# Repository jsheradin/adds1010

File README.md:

# adds1010
Modernization of an ADDS 1010 terminal keyboard

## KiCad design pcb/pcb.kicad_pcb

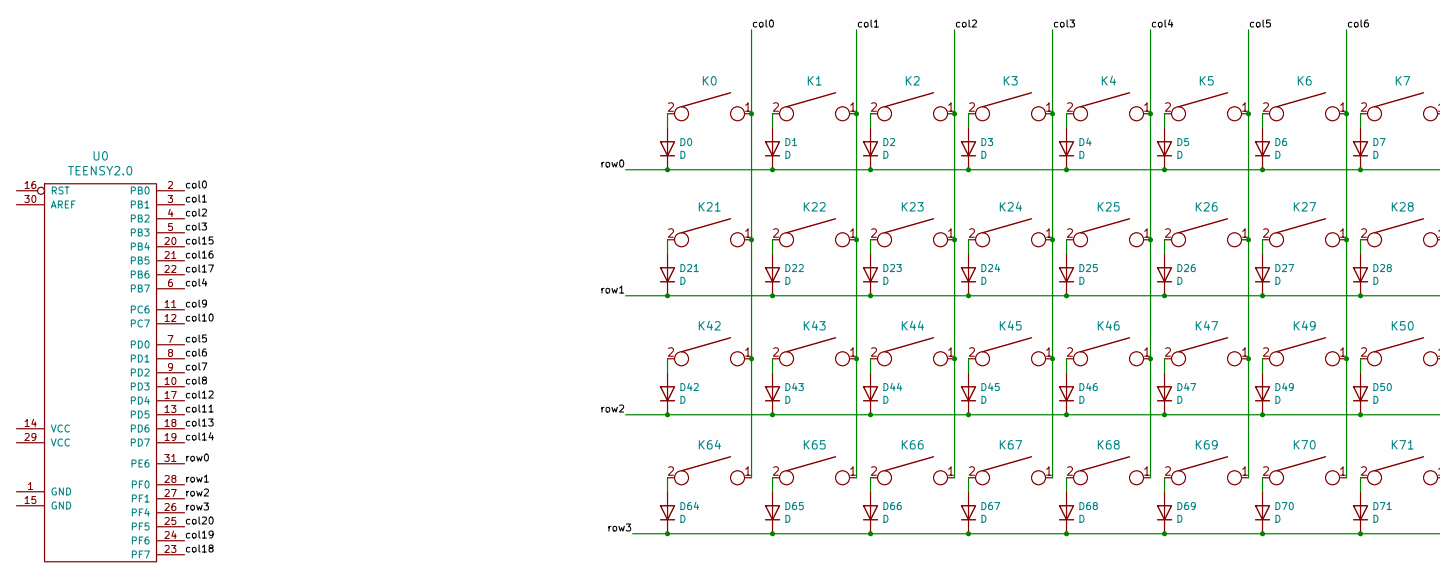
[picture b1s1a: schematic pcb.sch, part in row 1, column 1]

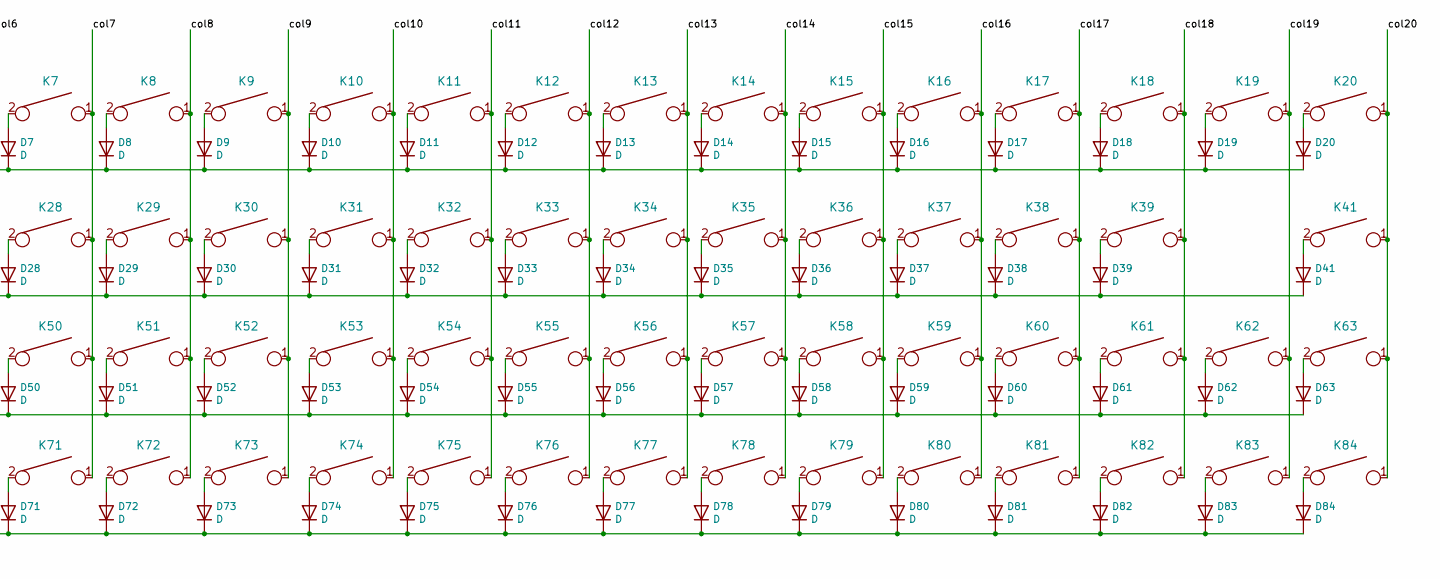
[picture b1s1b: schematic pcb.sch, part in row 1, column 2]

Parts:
D0, D1, D2, D3, D4, D5, D6, D7, D8, D9, D10, D11, D12, D13, D14, D15, D16, D17, D18, D19, D20, D21, D22, D23, D24, D25, D26, D27, D28, D29, D30, D31, D32, D33, D34, D35, D36, D37, D38, D39, D41, D42, D43, D44, D45, D46, D47, D49, D50, D51, D52, D53, D54, D55, D56, D57, D58, D59, D60, D61, D62, D63, D64, D65, D66, D67, D68, D69, D70, D71, D72, D73, D74, D75, D76, D77, D78, D79, D80, D81, D82, D83, D84: D; D_SOD123_axial
K0, K1, K2, K3, K4, K5, K6, K7, K8, K9, K10, K11, K12, K13, K14, K15, K16, K17, K18, K19, K20, K21, K22, K23, K24, K25, K26, K27, K28, K29, K30, K31, K32, K33, K34, K35, K36, K37, K38, K39, K41, K42, K43, K44, K45, K46, K47, K49, K50, K51, K52, K53, K54, K55, K56, K57, K58, K59, K60, K61, K62, K63, K64, K65, K66, K67, K68, K69, K70, K71, K72, K73, K74, K75, K76, K77, K78, K79, K80, K81, K82, K83, K84: KEYSW; Space_Invaders
U0: TEENSY2.0; Teensy2.0

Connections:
/col0: K0.1, K21.1, K42.1, K64.1, U0.2 (PB0)
/col1: K1.1, K22.1, K43.1, K65.1, U0.3 (PB1)
/col2: K2.1, K23.1, K44.1, K66.1, U0.4 (PB2)
/col3: K3.1, K24.1, K45.1, K67.1, U0.5 (PB3)
/col4: K4.1, K25.1, K46.1, K68.1, U0.6 (PB7)
/col5: K5.1, K26.1, K47.1, K69.1, U0.7 (PD0)
/col6: K6.1, K27.1, K49.1, K70.1, U0.8 (PD1)
/col7: K7.1, K28.1, K50.1, K71.1, U0.9 (PD2)
/col8: K8.1, K29.1, K51.1, K72.1, U0.10 (PD3)
/col9: K9.1, K30.1, K52.1, K73.1, U0.11 (PC6)
/col10: K10.1, K31.1, K53.1, K74.1, U0.12 (PC7)
/col11: K11.1, K32.1, K54.1, K75.1, U0.13 (PD5)
/col12: K12.1, K33.1, K55.1, K76.1, U0.17 (PD4)
/col13: K13.1, K34.1, K56.1, K77.1, U0.18 (PD6)
/col14: K14.1, K35.1, K57.1, K78.1, U0.19 (PD7)
/col15: K15.1, K36.1, K58.1, K79.1, U0.20 (PB4)
/col16: K16.1, K37.1, K59.1, K80.1, U0.21 (PB5)
/col17: K17.1, K38.1, K60.1, K81.1, U0.22 (PB6)
/col18: K18.1, K39.1, K61.1, K82.1, U0.23 (PF7)
/col19: K19.1, K62.1, K83.1, U0.24 (PF6)
/col20: K20.1, K41.1, K63.1, K84.1, U0.25 (PF5)
/row0: D0.1 (K), D1.1 (K), D2.1 (K), D3.1 (K), D4.1 (K), D5.1 (K), D6.1 (K), D7.1 (K), D8.1 (K), D9.1 (K), D10.1 (K), D11.1 (K), D12.1 (K), D13.1 (K), D14.1 (K), D15.1 (K), D16.1 (K), D17.1 (K), D18.1 (K), D19.1 (K), D20.1 (K), U0.31 (PE6)
/row1: D21.1 (K), D22.1 (K), D23.1 (K), D24.1 (K), D25.1 (K), D26.1 (K), D27.1 (K), D28.1 (K), D29.1 (K), D30.1 (K), D31.1 (K), D32.1 (K), D33.1 (K), D34.1 (K), D35.1 (K), D36.1 (K), D37.1 (K), D38.1 (K), D39.1 (K), D41.1 (K), U0.28 (PF0)
/row2: D42.1 (K), D43.1 (K), D44.1 (K), D45.1 (K), D46.1 (K), D47.1 (K), D49.1 (K), D50.1 (K), D51.1 (K), D52.1 (K), D53.1 (K), D54.1 (K), D55.1 (K), D56.1 (K), D57.1 (K), D58.1 (K), D59.1 (K), D60.1 (K), D61.1 (K), D62.1 (K), D63.1 (K), U0.27 (PF1)
/row3: D64.1 (K), D65.1 (K), D66.1 (K), D67.1 (K), D68.1 (K), D69.1 (K), D70.1 (K), D71.1 (K), D72.1 (K), D73.1 (K), D74.1 (K), D75.1 (K), D76.1 (K), D77.1 (K), D78.1 (K), D79.1 (K), D80.1 (K), D81.1 (K), D82.1 (K), D83.1 (K), D84.1 (K), U0.26 (PF4)
unnamed: D0.2 (A), K0.2
unnamed: D1.2 (A), K1.2
unnamed: D2.2 (A), K2.2
unnamed: D3.2 (A), K3.2
unnamed: D4.2 (A), K4.2
unnamed: D5.2 (A), K5.2
unnamed: D6.2 (A), K6.2
unnamed: D7.2 (A), K7.2
unnamed: D8.2 (A), K8.2
unnamed: D9.2 (A), K9.2
unnamed: D10.2 (A), K10.2
unnamed: D11.2 (A), K11.2
unnamed: D12.2 (A), K12.2
unnamed: D13.2 (A), K13.2
unnamed: D14.2 (A), K14.2
unnamed: D15.2 (A), K15.2
unnamed: D16.2 (A), K16.2
unnamed: D17.2 (A), K17.2
unnamed: D18.2 (A), K18.2
unnamed: D19.2 (A), K19.2
unnamed: D20.2 (A), K20.2
unnamed: D21.2 (A), K21.2
unnamed: D22.2 (A), K22.2
unnamed: D23.2 (A), K23.2
unnamed: D24.2 (A), K24.2
unnamed: D25.2 (A), K25.2
unnamed: D26.2 (A), K26.2
unnamed: D27.2 (A), K27.2
unnamed: D28.2 (A), K28.2
unnamed: D29.2 (A), K29.2
unnamed: D30.2 (A), K30.2
unnamed: D31.2 (A), K31.2
unnamed: D32.2 (A), K32.2
unnamed: D33.2 (A), K33.2
unnamed: D34.2 (A), K34.2
unnamed: D35.2 (A), K35.2
unnamed: D36.2 (A), K36.2
unnamed: D37.2 (A), K37.2
unnamed: D38.2 (A), K38.2
unnamed: D39.2 (A), K39.2
unnamed: D41.2 (A), K41.2
unnamed: D42.2 (A), K42.2
unnamed: D43.2 (A), K43.2
unnamed: D44.2 (A), K44.2
unnamed: D45.2 (A), K45.2
unnamed: D46.2 (A), K46.2
unnamed: D47.2 (A), K47.2
unnamed: D49.2 (A), K49.2
unnamed: D50.2 (A), K50.2
unnamed: D51.2 (A), K51.2
unnamed: D52.2 (A), K52.2
unnamed: D53.2 (A), K53.2
unnamed: D54.2 (A), K54.2
unnamed: D55.2 (A), K55.2
unnamed: D56.2 (A), K56.2
unnamed: D57.2 (A), K57.2
unnamed: D58.2 (A), K58.2
unnamed: D59.2 (A), K59.2
unnamed: D60.2 (A), K60.2
unnamed: D61.2 (A), K61.2
unnamed: D62.2 (A), K62.2
unnamed: D63.2 (A), K63.2
unnamed: D64.2 (A), K64.2
unnamed: D65.2 (A), K65.2
unnamed: D66.2 (A), K66.2
unnamed: D67.2 (A), K67.2
unnamed: D68.2 (A), K68.2
unnamed: D69.2 (A), K69.2
unnamed: D70.2 (A), K70.2
unnamed: D71.2 (A), K71.2
unnamed: D72.2 (A), K72.2
unnamed: D73.2 (A), K73.2
unnamed: D74.2 (A), K74.2
unnamed: D75.2 (A), K75.2
unnamed: D76.2 (A), K76.2
unnamed: D77.2 (A), K77.2
unnamed: D78.2 (A), K78.2
unnamed: D79.2 (A), K79.2
unnamed: D80.2 (A), K80.2
unnamed: D81.2 (A), K81.2
unnamed: D82.2 (A), K82.2
unnamed: D83.2 (A), K83.2
unnamed: D84.2 (A), K84.2

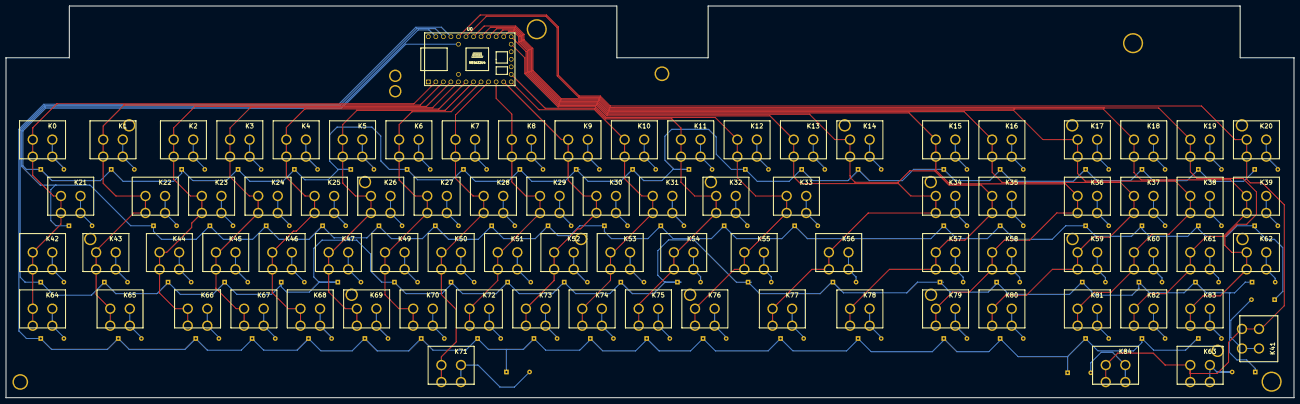
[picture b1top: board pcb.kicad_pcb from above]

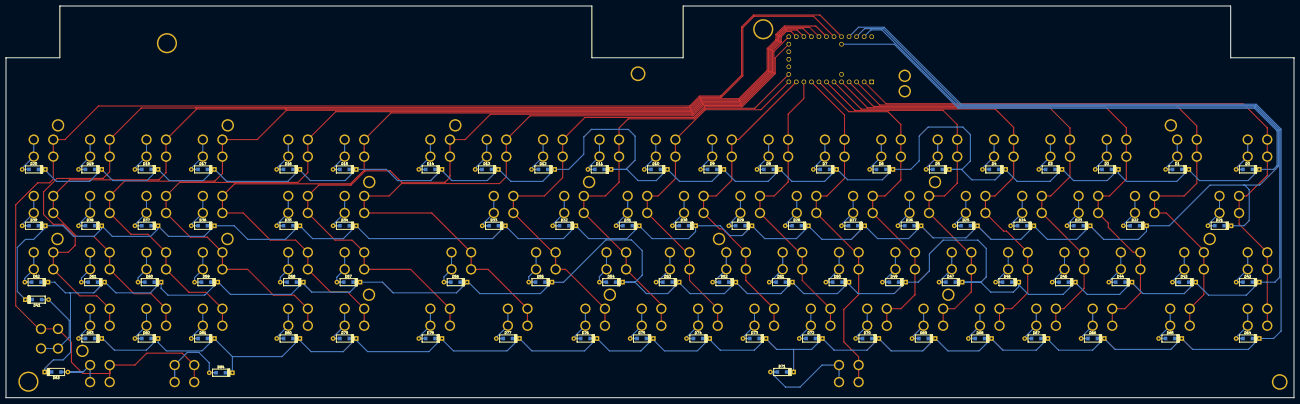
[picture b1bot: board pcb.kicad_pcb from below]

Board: 2 copper layers, 434.2 x 132.0 mm, 189 parts (83 on the bottom side), 108 nets.

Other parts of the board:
3.0mm, 3.0mm#2, 3.0mm#3, 3.0mm#4, 3.0mm#5, 3.0mm#6, 3.0mm#7, 3.0mm#8, 3.0mm#9, 3.0mm#10, 3.0mm#11, 3.0mm#12, 3.0mm#13, 3.0mm#14, 3.0mm#15, 3.0mm#16, 3.0mm#17: VAL**; Hole_3.0mm
3.8mm: VAL**; Hole_3.8mm
4.1mm: VAL**; Hole_4.1mm
5.6mm, 5.6mm#2, 5.6mm#3: VAL**; Hole_5.6mm

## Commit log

2021-04-13 Add project files
2021-04-13 Remove lock file
